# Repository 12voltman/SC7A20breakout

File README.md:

</img>
# SC7A20breakout
Breakout for the SC7A20 low-cost 3-axis accelerometer  
## Features
- 12-bit range
- ±2G, ±4G, ±8G, ±16G selectable range
- 1-400Hz poll rate
- 1.7-3.6V operating voltage
- I<sup>2</sup>C/SPI/3-Wire SPI selectable interface
- 2 independent interrupts
- On-board 10k I<sup>2</sup>C pullups (cut jumper to disable)
- On-board power LED (cut jumper to disable)  
</img> </img>

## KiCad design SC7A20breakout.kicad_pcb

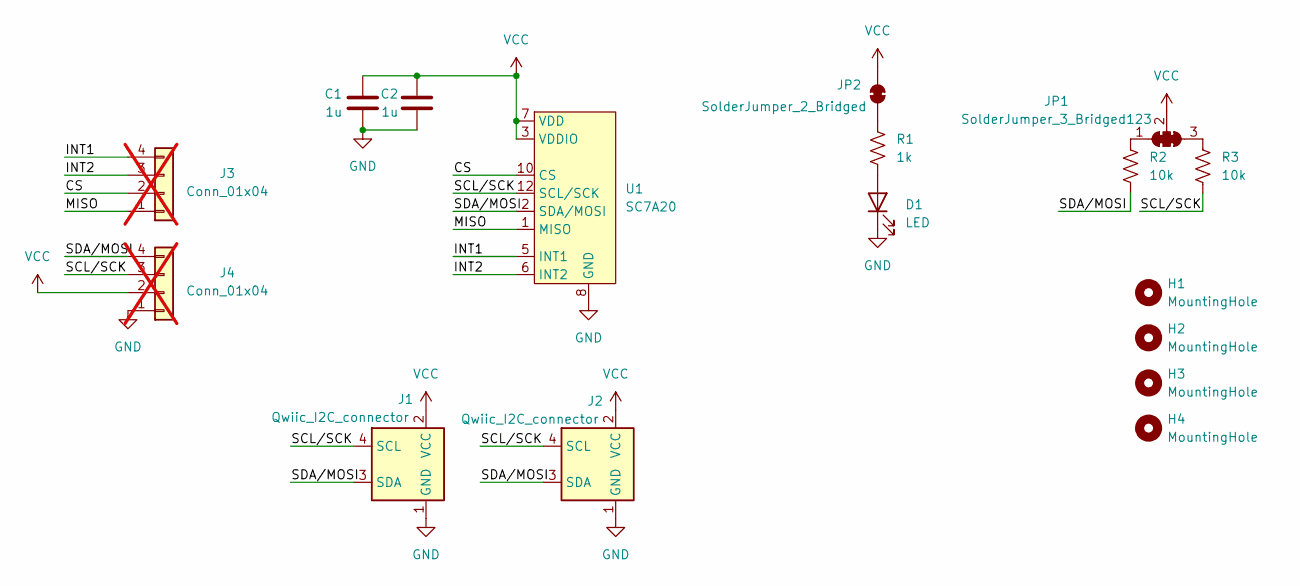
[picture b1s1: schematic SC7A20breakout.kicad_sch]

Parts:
C1, C2: 1u; C_0603_1608Metric; LCSC C15849
D1: LED; LED_0603_1608Metric; LCSC C2286
H1, H2, H3, H4: MountingHole; MountingHole_3.2mm_M3
J1, J2: Qwiic_I2C_connector; JST_SH_SM04B-SRSS-TB_1x04-1MP_P1.00mm_Horizontal; LCSC C7430446
J3, J4: Conn_01x04; PinHeader_1x04_P2.54mm_Vertical; not fitted
JP1: SolderJumper_3_Bridged123; SolderJumper-3_P1.3mm_Bridged123_RoundedPad1.0x1.5mm
JP2: SolderJumper_2_Bridged; SolderJumper-2_P1.3mm_Bridged_RoundedPad1.0x1.5mm
R1: 1k; R_0603_1608Metric; LCSC C21190
R2, R3: 10k; R_0603_1608Metric; LCSC C25804
U1: SC7A20; Kionix_LGA-12_2x2mm_P0.5mm_LayoutBorder2x4y; LCSC C5126709

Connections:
/CS: J3.2, U1.10 (CS)
/INT1: J3.4, U1.5 (INT1)
/INT2: J3.3, U1.6 (INT2)
/MISO: J3.1, U1.1 (MISO)
/SCL/SCK: J1.4 (SCL), J2.4 (SCL), J4.3, R3.2, U1.12 (SCL/SCK)
/SDA/MOSI: J1.3 (SDA), J2.3 (SDA), J4.4, R2.2, U1.2 (SDA/MOSI)
GND: C1.2, C2.2, D1.1 (K), J1.1 (GND), J1.MP (VSS), J2.1 (GND), J2.MP (VSS), J4.1, U1.8 (GND), U1.9 (GND)
unnamed: D1.2 (A), R1.2
unnamed: JP1.1 (A), R2.1
unnamed: JP1.3 (B), R3.1
unnamed: JP2.1 (A), R1.1
VCC: C1.1, C2.1, J1.2 (VCC), J2.2 (VCC), J4.2, JP1.2 (C), JP2.2 (B), U1.3 (VDDIO), U1.7 (VDD)

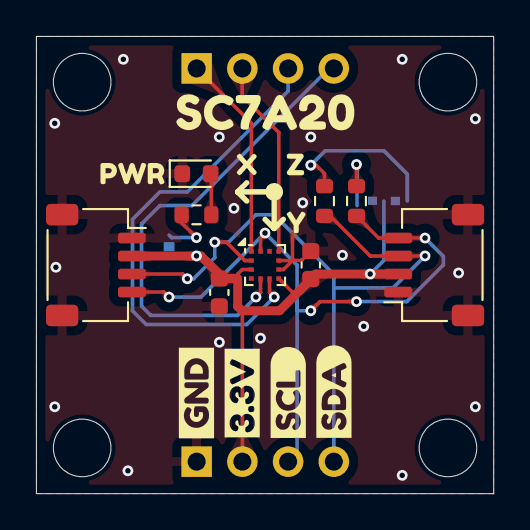
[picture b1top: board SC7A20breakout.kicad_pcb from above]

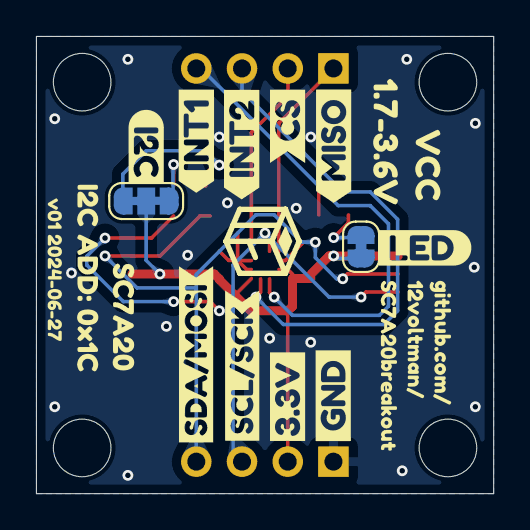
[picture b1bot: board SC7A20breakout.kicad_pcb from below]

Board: 2 copper layers, 25.4 x 25.4 mm, 40 parts (16 on the bottom side), 12 nets.

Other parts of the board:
kibuzzard-667CFAB6, kibuzzard-667CFAB6#2: G***; kibuzzard-667CFAB6
kibuzzard-667CFB53, kibuzzard-667CFB53#2: G***; kibuzzard-667CFB53
kibuzzard-667CFB75: G***; kibuzzard-667CFB75
kibuzzard-667CFBC3: G***; kibuzzard-667CFBC3
kibuzzard-667CFC6D: G***; kibuzzard-667CFC6D
kibuzzard-667CFC83: G***; kibuzzard-667CFC83
kibuzzard-667CFD0E: G***; kibuzzard-667CFD0E
kibuzzard-667CFD1C: G***; kibuzzard-667CFD1C
kibuzzard-667CFD41: G***; kibuzzard-667CFD41
kibuzzard-667CFD49: G***; kibuzzard-667CFD49
kibuzzard-667CFEC2: G***; kibuzzard-667CFEC2
kibuzzard-667D04C9: G***; kibuzzard-667D04C9
kibuzzard-667D053C: G***; kibuzzard-667D053C
kibuzzard-667D0532: G***; kibuzzard-667D0532
kibuzzard-667D0544: G***; kibuzzard-667D0544
kibuzzard-667DD6C5: G***; kibuzzard-667DD6C5
kibuzzard-667DDCB5: G***; kibuzzard-667DDCB5
kibuzzard-667DE64B: G***; kibuzzard-667DE64B
kibuzzard-667DE68B: G***; kibuzzard-667DE68B
kibuzzard-667DFE26: G***; kibuzzard-667DFE26
kibuzzard-667DFE33: G***; kibuzzard-667DFE33

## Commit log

2024-06-27 Preliminary revision PCB
2024-06-28 Correct hole spacing and labeling
2024-06-28 Added pictures
2024-06-28 Added images to README.md
2024-06-28 Ignored production files
2024-06-28 Switched to JLCPCB basic assembly parts
